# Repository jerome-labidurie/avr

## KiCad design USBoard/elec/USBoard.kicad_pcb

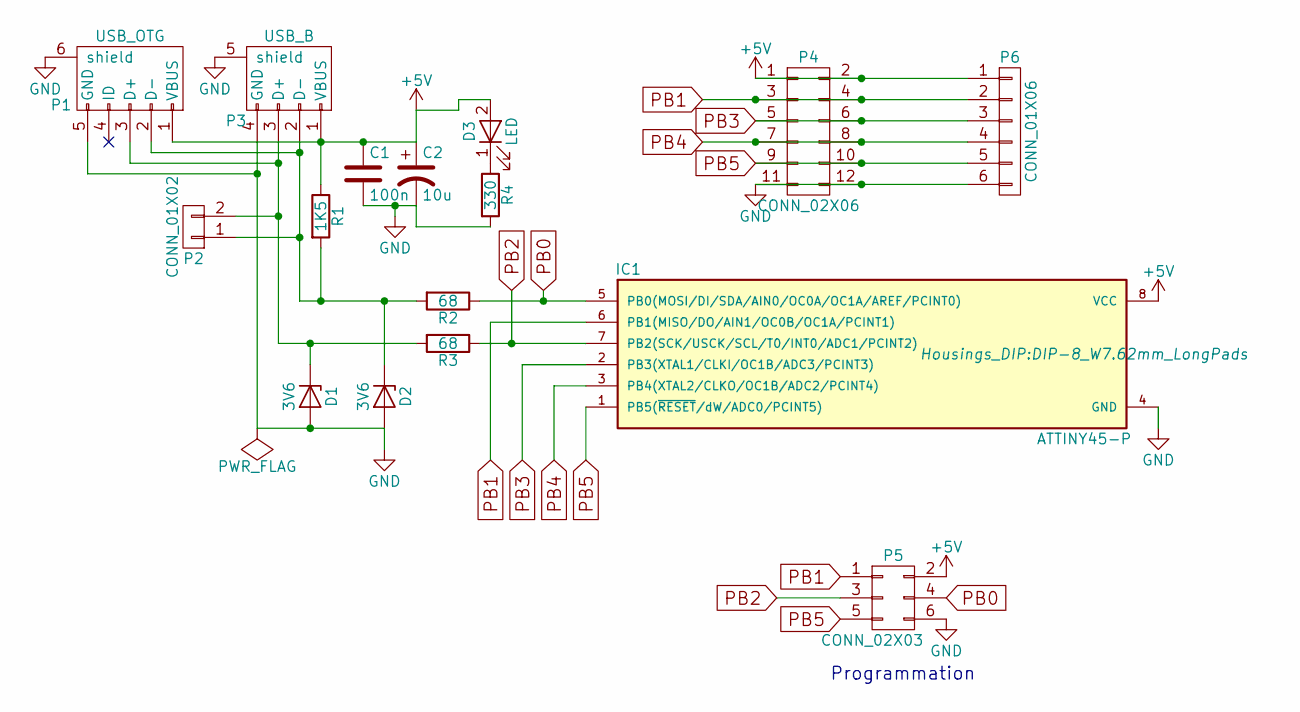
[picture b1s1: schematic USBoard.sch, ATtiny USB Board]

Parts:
C1: 100n; C_Disc_D6_P5
C2: 10u; C_Radial_D5_L11_P2.5
D1, D2: 3V6; Diode_DO-35_SOD27_Horizontal_RM10
D3: LED; LED-3MM
IC1: ATTINY45-P; DIP-8_W7.62mm_LongPads
P1: USB_OTG; USB_Micro-B
P2: CONN_01X02; PINHEAD1-2
P3: USB_B
P4: CONN_02X06; IDC_Header_Straight_12pins
P5: CONN_02X03; PinHeader_2x03_P2.54mm_Vertical
P6: CONN_01X06; PINHEAD1-6
R1: 1K5; Resistor_Horizontal_RM7mm
R2, R3: 68; Resistor_Horizontal_RM7mm
R4: 330; Resistor_Horizontal_RM7mm

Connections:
+5V: C1.1, C2.1, D3.2 (A), IC1.8 (VCC), P1.1 (VBUS), P3.1 (VBUS), P4.1, P4.2, P5.2, P6.1, R1.1
GND: C1.2, C2.2, D1.2 (A), D2.2 (A), IC1.4 (GND), P1.5 (GND), P1.6 (shield), P3.4 (GND), P3.5 (shield), P4.11, P4.12, P5.6, P6.6, R4.2
unnamed: D1.1 (K), P1.3 (D+), P2.2, P3.3 (D+), R3.2
unnamed: D2.1 (K), P1.2 (D-), P2.1, P3.2 (D-), R1.2, R2.2
unnamed: D3.1 (K), R4.1
PB0: IC1.5 (PB0(MOSI/DI/SDA/AIN0/OC0A/OC1A/AREF/PCI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), P5.4, R2.1
PB1: IC1.6 (PB1(MISO/DO/AIN1/OC0B/OC1A/PCINT1)), P4.3, P4.4, P5.1, P6.2
PB2: IC1.7 (PB2(SCK/USCK/SCL/T0/INT0/ADC1/PCINT2)), P5.3, R3.1
PB3: IC1.2 (PB3(XTAL1/CLKI/OC1B/ADC3/PCINT3)), P4.5, P4.6, P6.3
PB4: IC1.3 (PB4(XTAL2/CLKO/OC1B/ADC2/PCINT4)), P4.7, P4.8, P6.4
PB5: IC1.1 (PB5(~RESET~/dW/ADC0/PCINT5)), P4.9, P4.10, P5.5, P6.5

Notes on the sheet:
Programmation

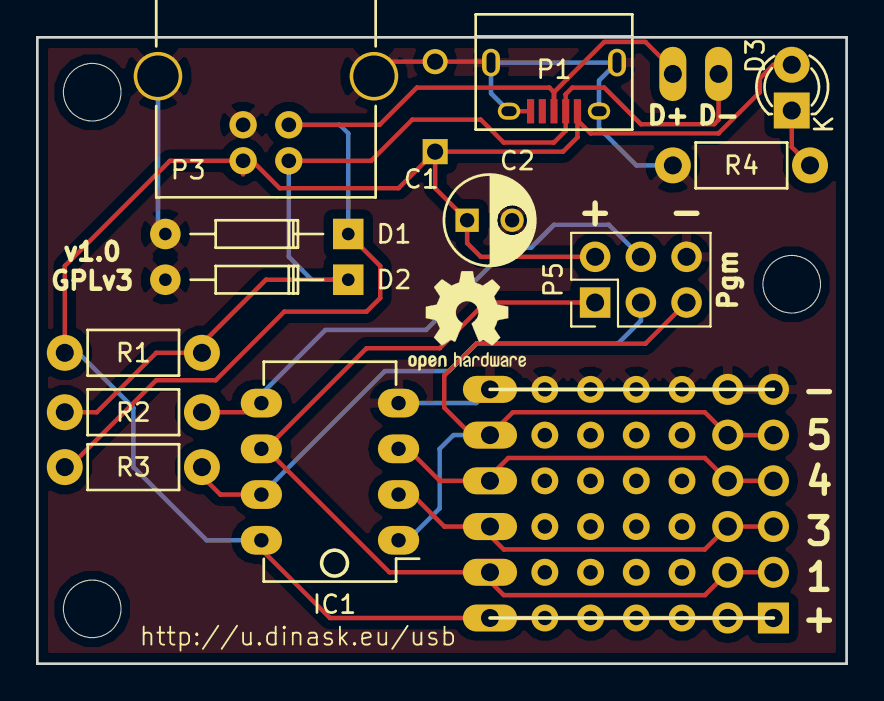
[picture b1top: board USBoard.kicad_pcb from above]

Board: 2 copper layers, 45.0 x 34.8 mm, 16 parts (0 on the bottom side), 11 nets.

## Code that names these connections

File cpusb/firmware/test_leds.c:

/** test leds and mux driver
 * Licence GPLv2 http://www.gnu.org/licenses/gpl-2.0.html
 */

/*********************************************************************************************
 * ATtiny45
 *                                      ---v---
 *         (PCINT5/RESET/ADC0/dW) PB5 -| 1   8 |- VCC
 *  (PCINT3/XTAL1/CLKI/OC1B/ADC3) PB3 -| 2   7 |- PB2 (SCK/USCK/SCL/ADC1/T0/INT0/PCINT2)
 *  (PCINT4/XTAL2/CLKO/OC1B/ADC2) PB4 -| 3   6 |- PB1 (MISO/DO/AIN1/OC0B/OC1A/PCINT1)
 *                                GND -| 4   5 |- PB0 (MOSI/DI/SDA/AIN0/OC0A/OC1A/AREF/PCINT0)
 *                                      -------
 * 
 **********************************************************************************************/


#include <stdio.h>
#include <stdlib.h>
#include <stdint.h>
#include <util/delay.h>
#include <avr/io.h>

#include "mux.h"

/** MAIN
 */
int main (void)
{  
   uint8_t i = 0;
   
   mux_init();
   
   while ( 1 )
   {
      switch (rand() % 6)
      {
         case 0:
            // K2000 chenillard
            for (i=0; i<8; i++) {
               mux_write(1<<i);
               _delay_ms (100);
            }
            for (i=7; i>0; i--) {
               mux_write(1<<(i-1));
               _delay_ms (100);
            }
            break;
         case 1:
            // allume les tous
            for (i=0; i<8; i++) {
               mux_set(i);
               _delay_ms (100);
            }
            // eteinds les tous
            for (i=7; i>0; i--) {
               mux_unset(i);
               _delay_ms (100);
            }
            break;
         case 2:
            // allume les tous
            for (i=0; i<8; i++) {
               mux_set(i);
               _delay_ms (100);
            }
            // eteinds les tous
            for (i=0; i<8; i++) {
               mux_unset(i);
               _delay_ms (100);
            }
            break;
         case 3:
            // allume les tous
            for (i=8; i>0; i--) {
               mux_set(i-1);
               _delay_ms (100);
            }
            // eteinds les tous
            for (i=0; i<8; i++) {
               mux_unset(i);
               _delay_ms (100);
            }
            break;
         case 4:
            for (i=0; i<5; i++) {
               mux_write (0xFF);
               _delay_ms (500);
               mux_write (0x00);
               _delay_ms (500);
            }
            break;
         default:
            break;
      }
   }

   return (0);
} /* main */

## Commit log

2013-11-29 hardware scheme
2013-11-29 hardware readme
2013-11-29 cpusb hardware scheme
2015-09-25 Add pdf for scheme
2018-08-05 Add volumeKnob
2018-08-05 add USBoard
2018-08-05 update gitignore
2018-08-05 add licence
2018-08-05 Add silk & properties
2020-05-23 Add inter disable around calib
2020-05-23 Updt box
2020-05-23 remove old box

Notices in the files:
USBoard/elec/USBoard.kicad_pcb:
GPLv3
